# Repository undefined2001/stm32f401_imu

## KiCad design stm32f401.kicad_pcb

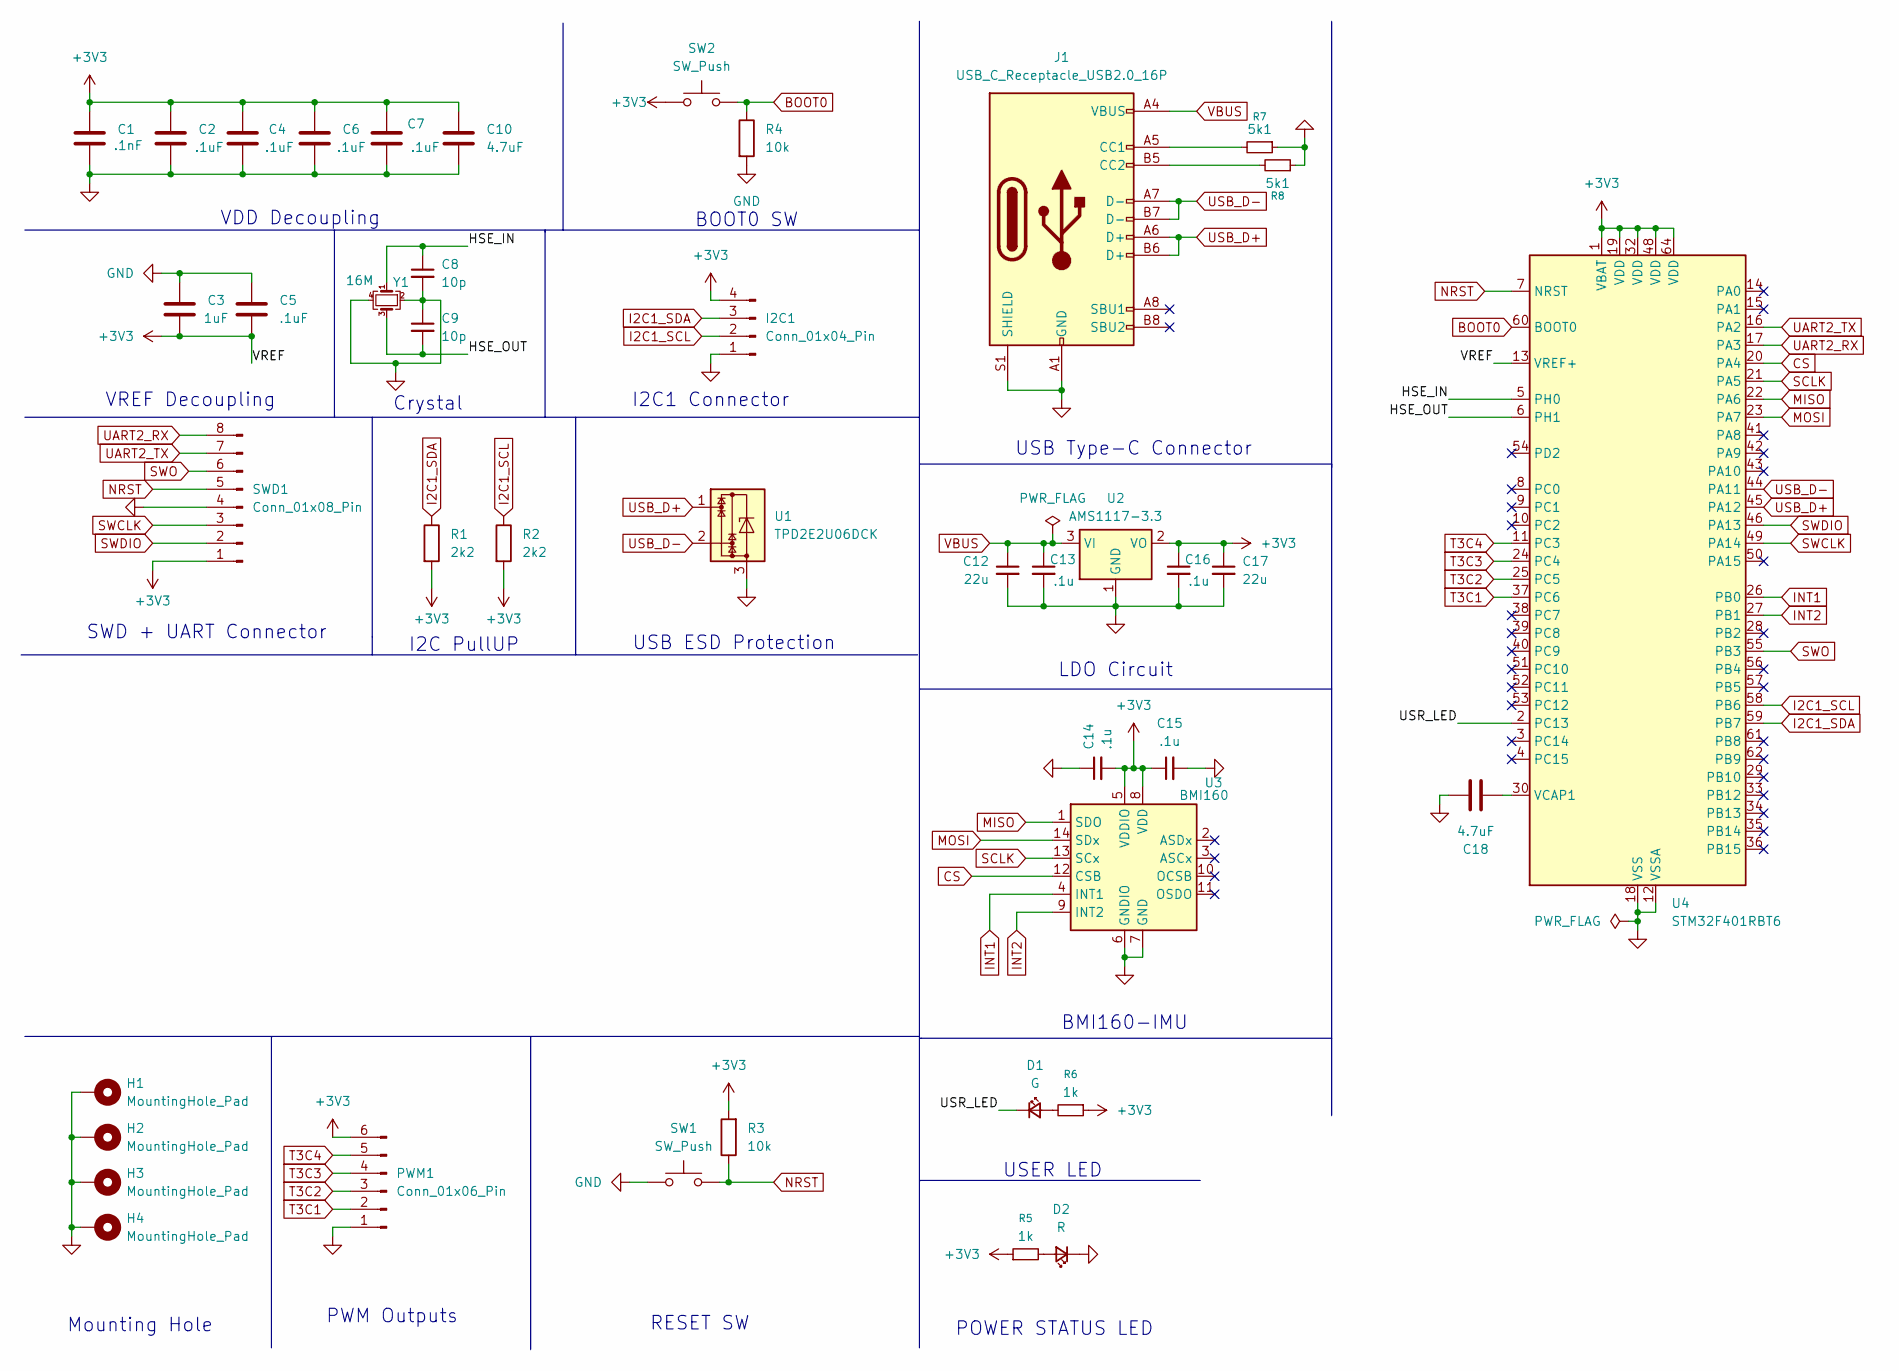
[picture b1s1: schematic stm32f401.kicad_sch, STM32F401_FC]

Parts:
C1: .1nF; C_0402_1005Metric
C2, C4, C5, C6, C7: .1uF; C_0402_1005Metric
C3: 1uF; C_0603_1608Metric
C8, C9: 10p; C_0402_1005Metric
C10, C18: 4.7uF; C_0603_1608Metric
C12, C17: 22u; C_0603_1608Metric
C13, C14, C15, C16: .1u; C_0402_1005Metric
D1: G; LED_0402_1005Metric
D2: R; LED_0402_1005Metric
H1, H2, H3, H4: MountingHole_Pad; MountingHole_2.5mm_Pad_Via
I2C1: Conn_01x04_Pin; JST_SH_SM04B-SRSS-TB_1x04-1MP_P1.00mm_Horizontal
J1: USB_C_Receptacle_USB2.0_16P; USB_C_Receptacle_GCT_USB4105-xx-A_16P_TopMnt_Horizontal
PWM1: Conn_01x06_Pin; JST_SH_SM06B-SRSS-TB_1x06-1MP_P1.00mm_Horizontal
R1, R2: 2k2; R_0402_1005Metric
R3, R4: 10k; R_0402_1005Metric
R5, R6: 1k; R_0402_1005Metric
R7, R8: 5k1; R_0402_1005Metric
SW1, SW2: SW_Push; SW_SPST_B3U-1000P
SWD1: Conn_01x08_Pin; Conn_0x08
U1: TPD2E2U06DCK; SOT-323_SC-70
U2: AMS1117-3.3; SOT-223-3_TabPin2
U3: BMI160; Bosch_LGA-14_3x2.5mm_P0.5mm
U4: STM32F401RBT6; LQFP-64_10x10mm_P0.5mm
Y1: 16M; Crystal_SMD_3225-4Pin_3.2x2.5mm

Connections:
+3V3: C1.1, C2.1, C3.2, C4.1, C5.2, C6.1, C7.1, C10.1, C14.2, C15.1, C16.1, C17.1, I2C1.4, PWM1.6, R1.2, R2.2, R3.2, R5.1, R6.1, SW2.1, SWD1.1, U2.2 (VO), U3.5 (VDDIO), U3.8 (VDD), U4.1 (VBAT), U4.13 (VREF+), U4.19 (VDD), U4.32 (VDD), U4.48 (VDD), U4.64 (VDD); also elsewhere on the board
/HSE_IN: C8.1, U4.5 (PH0), Y1.1
/HSE_OUT: C9.2, U4.6 (PH1), Y1.3
/USR_LED: D1.1 (K), U4.2 (PC13)
BOOT0: R4.1, SW2.2, U4.60 (BOOT0); also elsewhere on the board
CS: U3.12 (CSB), U4.20 (PA4)
GND: C1.2, C2.2, C3.1, C4.2, C5.1, C6.2, C7.2, C8.2, C9.1, C10.2, C12.2, C13.2, C14.1, C15.2, C16.2, C17.2, C18.2, D2.1 (K), H1.1, H2.1, H3.1, H4.1, I2C1.1, J1.A1 (GND), J1.A12 (GND), J1.B1 (GND), J1.B12 (GND), J1.S1 (SHIELD), PWM1.1, R4.2, R7.1, R8.1, SW1.1, SWD1.4, U1.3, U2.1 (GND), U3.6 (GNDIO), U3.7 (GND), U4.12 (VSSA), U4.18 (VSS), U4.31 (VSS), U4.47 (VSS), U4.63 (VSS), Y1.2, Y1.4; also elsewhere on the board
I2C1_SCL: I2C1.2, R2.1, U4.58 (PB6)
I2C1_SDA: I2C1.3, R1.1, U4.59 (PB7)
INT1: U3.4 (INT1), U4.26 (PB0)
INT2: U3.9 (INT2), U4.27 (PB1)
MISO: U3.1 (SDO), U4.22 (PA6)
MOSI: U3.14 (SDx), U4.23 (PA7)
NRST: R3.1, SW1.2, SWD1.5, U4.7 (NRST); also elsewhere on the board
unnamed: D1.2 (A), R6.2
unnamed: D2.2 (A), R5.2
unnamed: J1.A5 (CC1), R7.2
unnamed: J1.B5 (CC2), R8.2
unnamed: C18.1, U4.30 (VCAP1)
SCLK: U3.13 (SCx), U4.21 (PA5)
SWCLK: SWD1.3, U4.49 (PA14); also elsewhere on the board
SWDIO: SWD1.2, U4.46 (PA13); also elsewhere on the board
SWO: SWD1.6, U4.55 (PB3); also elsewhere on the board
T3C1: PWM1.2, U4.37 (PC6)
T3C2: PWM1.3, U4.25 (PC5)
T3C3: PWM1.4, U4.24 (PC4)
T3C4: PWM1.5, U4.11 (PC3)
UART2_RX: SWD1.8, U4.17 (PA3); also elsewhere on the board
UART2_TX: SWD1.7, U4.16 (PA2); also elsewhere on the board
USB_D+: J1.A6 (D+), J1.B6 (D+), U1.1, U4.45 (PA12)
USB_D-: J1.A7 (D-), J1.B7 (D-), U1.2, U4.44 (PA11)
VBUS: C12.1, C13.1, J1.A4 (VBUS), J1.A9 (VBUS), J1.B4 (VBUS), J1.B9 (VBUS), U2.3 (VI)

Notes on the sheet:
Mounting Hole
PWM Outputs
POWER STATUS LED
SWD + UART Connector
USB Type-C Connector
VREF Decoupling
RESET SW
I2C PullUP
USB ESD Protection
BOOT0 SW
I2C1 Connector
Crystal
USER LED
VDD Decoupling
LDO Circuit
BMI160-IMU

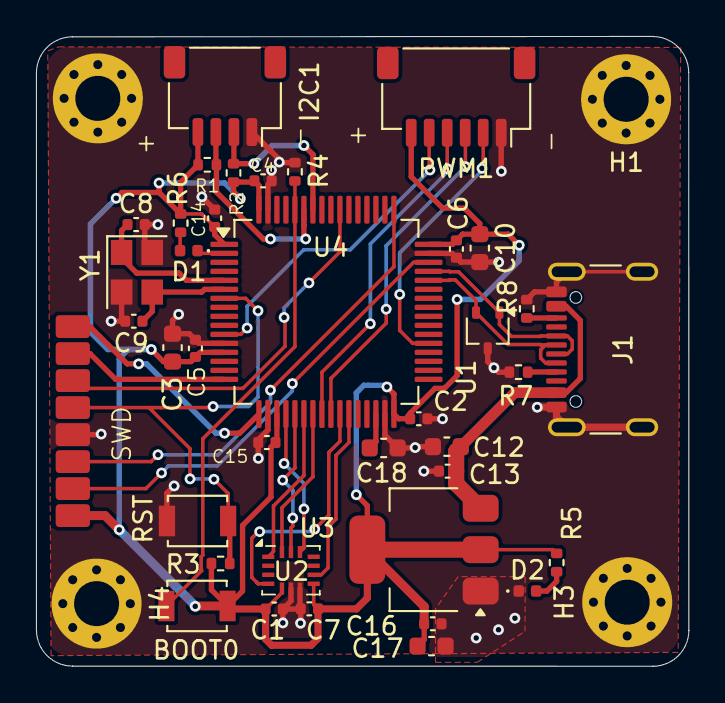
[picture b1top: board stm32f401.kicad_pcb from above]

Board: 2 copper layers, 36.2 x 35.0 mm, 42 parts (0 on the bottom side), 32 nets.

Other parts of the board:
BOOT0: SW_Push; SW_SPST_B3U-1000P
RST: SW_Push; SW_SPST_B3U-1000P
SWD: Conn_01x08_Pin; Conn_0x08

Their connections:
+3V3: BOOT0.1, SWD.1; also elsewhere on the board
BOOT0: BOOT0.2; also elsewhere on the board
GND: RST.1, SWD.4; also elsewhere on the board
NRST: RST.2, SWD.5; also elsewhere on the board
SWCLK: SWD.3; also elsewhere on the board
SWDIO: SWD.2; also elsewhere on the board
SWO: SWD.6; also elsewhere on the board
UART2_RX: SWD.8; also elsewhere on the board
UART2_TX: SWD.7; also elsewhere on the board

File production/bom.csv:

Designator,Footprint,Quantity,Value,LCSC Part #
"BOOT0, RST",SW_SPST_B3U-1000P,2,SW_Push,
C1,0402,1,.1nF,
"C10, C18",0603,2,4.7uF,
"C12, C17",0603,2,22u,
"C13, C14, C15, C16",0402,4,.1u,
"C2, C4, C5, C6, C7",0402,5,.1uF,
C3,0603,1,1uF,
"C8, C9",0402,2,10p,
D1,0402,1,G,
D2,0402,1,R,
I2C1,JST_SH_SM04B-SRSS-TB_1x04-1MP_P1.00mm_Horizontal,1,Conn_01x04_Pin,
J1,USB_C_Receptacle_GCT_USB4105-xx-A_16P_TopMnt_Horizontal,1,USB_C_Receptacle_USB2.0_16P,
PWM1,JST_SH_SM06B-SRSS-TB_1x06-1MP_P1.00mm_Horizontal,1,Conn_01x06_Pin,
"R1, R2",0402,2,2k2,
"R3, R4",0402,2,10k,
"R5, R6",0402,2,1k,
"R7, R8",0402,2,5k1,
SWD,Conn_0x08,1,Conn_01x08_Pin,
U1,SOT-323_SC-70,1,TPD2E2U06DCK,
U2,SOT-223-3_TabPin2,1,AMS1117-3.3,
U3,Bosch_LGA-14_3x2.5mm_P0.5mm,1,BMI160,
U4,LQFP-64_10x10mm_P0.5mm,1,STM32F401RBT6,
Y1,Crystal_SMD_3225-4Pin_3.2x2.5mm,1,16M,

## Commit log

2025-04-28 Initial PCB Design
